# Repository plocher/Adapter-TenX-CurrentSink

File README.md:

# Adapter-TenX-CurrentSink
## License: Creative Commons Attribution-NonCommercial-ShareAlike

Experimental high current output expansion board adapter for MRCS cpNode evolution

initial version

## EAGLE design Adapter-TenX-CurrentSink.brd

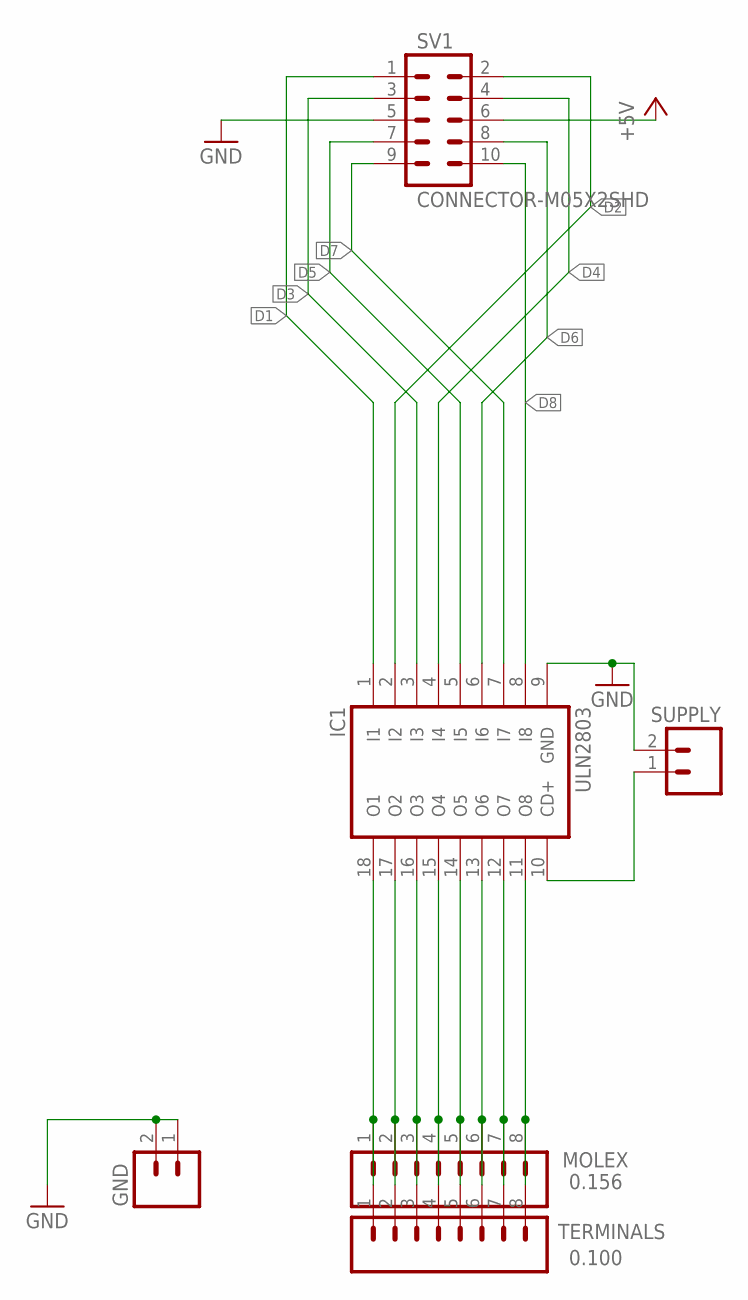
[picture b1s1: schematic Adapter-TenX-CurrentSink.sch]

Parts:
GND: M02POLAR_LOCK; MOLEX-1X2_LOCK
IC1: ULN2803; DIL18
MOLEX: 0.156; KK-156-8-M
SUPPLY: M02POLAR_LOCK; MOLEX-1X2_LOCK
SV1: CONNECTOR-M05X2SHD; 2X5-SHROUDED
TERMINALS: 0.100; 1X08_LOCK_LONGPADS

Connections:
+5V: SV1.6
D1: IC1.1 (I1), SV1.1
D2: IC1.2 (I2), SV1.2
D3: IC1.3 (I3), SV1.3
D4: IC1.4 (I4), SV1.4
D5: IC1.5 (I5), SV1.7
D6: IC1.6 (I6), SV1.8
D7: IC1.7 (I7), SV1.9
D8: IC1.8 (I8), SV1.10
GND: GND.1, GND.2, IC1.9 (GND), SUPPLY.2, SV1.5
unnamed: IC1.10 (CD+), SUPPLY.1
unnamed: IC1.18 (O1), MOLEX.1, TERMINALS.1
unnamed: IC1.17 (O2), MOLEX.2, TERMINALS.2
unnamed: IC1.16 (O3), MOLEX.3, TERMINALS.3
unnamed: IC1.15 (O4), MOLEX.4, TERMINALS.4
unnamed: IC1.14 (O5), MOLEX.5, TERMINALS.5
unnamed: IC1.13 (O6), MOLEX.6, TERMINALS.6
unnamed: IC1.12 (O7), MOLEX.7, TERMINALS.7
unnamed: IC1.11 (O8), MOLEX.8, TERMINALS.8

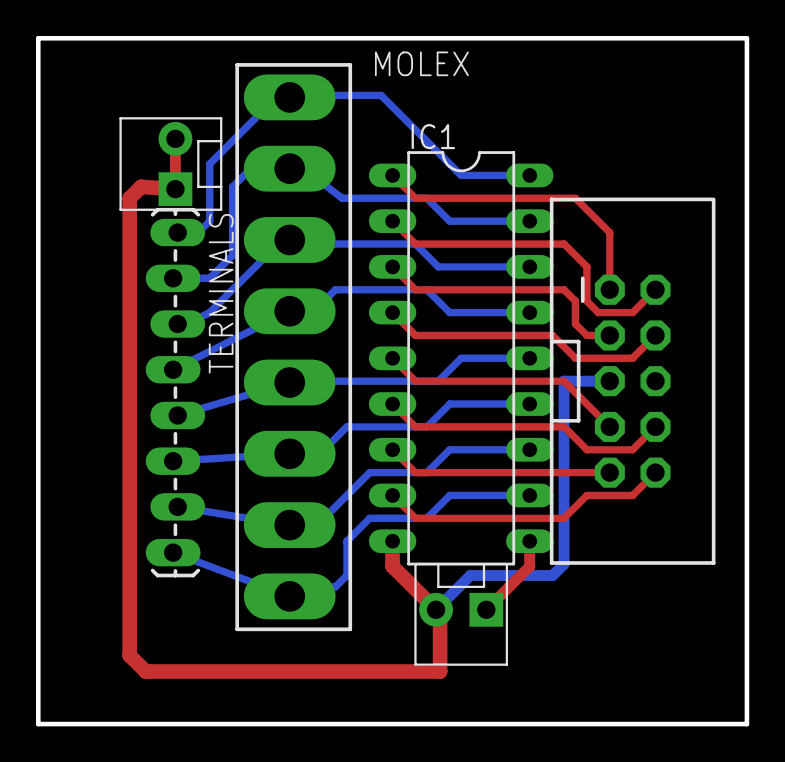
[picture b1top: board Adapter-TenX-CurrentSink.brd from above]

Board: 2 copper layers, 39.4 x 38.1 mm, 6 parts (0 on the bottom side), 18 nets.

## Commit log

2020-05-04 updated tags
